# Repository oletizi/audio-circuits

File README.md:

# Audio Circuits

A collection of audio circuits under development. Some are core, reusable
components meant to appear in future designs; some are designs in their own
right. Nothing here is finished software — it is hardware in progress.

## What this repository is for

**It is for carrying a circuit from a model to something buildable, with agents
doing that work end to end:**

- **A circuit is held as data** — built with `lib/model/`'s `circuit()` builder
  or read from a KiCad netlist — where it can be validated, simulated in SPICE,
  composed, partitioned and checked.
- **The KiCad and VeroRoute interfaces are driven by agents too**, which
  arrange schematics and place and route layouts for stripboard, perfboard and
  manufactured PCBs. Until 2026-10-10 this file said the opposite — that those
  were a person's work because agents are bad at hardware design. That is no
  longer the project's position; see
  `docs/superpowers/specs/2026-10-08-agent-authored-boards-design.md`.
- **What an agent never does is set the bar its own artifact is measured
  against.** Acceptance criteria come from a rule file, a spec, or a reviewing
  agent that did not produce the artifact. That constraint is the one thing kept
  from the older arrangement, because the failure it prevents is real: an agent
  that writes its own criteria from the layout it already produced will pass
  every check it set itself.

Authority runs in both directions depending on where a circuit came from. For a
circuit an agent designs, the model is authoritative and the drawing is derived
from it. The Pultec runs the other way: an existing design imported
schematic-first, with the model derived from a netlist export.

**A `.kicad_sch` is not written by code in this repository.** It is drawn by
`TOOLING.md`'s loop — copperhead drafts, akcli-kicad repairs, `kicad-cli`
renders and exports, the reviewer gives a verdict on the rendered page, and the
page is committed under `drafted/<circuit>/<board>/` beside a `RECORD.md`
carrying the sha256 the verdict is bound to.

> **This paragraph described a model-to-schematic generator at `lib/schgen/`
> with `bun run schgen` as its front door, and a superseded stub writer at
> `lib/kicad/schematic.ts` kept alive for the `transistor-preamp` round trips.
> All of it is deleted** — `lib/schgen/`, `tools/schgen/`, `tests/schgen/`,
> `lib/kicad/schematic.ts` and the three `schgen` CLI verbs — in the plan at
> `docs/superpowers/plans/2026-10-30-remove-schgen.md`, with the findings in
> `docs/research/2026-10-30-schgen-removed.md`. **The `kicad-cli` proof the stub
> was being kept for did not have to die with it — but it did change subject.**
> The old tests wrote a fresh throwaway stub from the live model and exported
> that, so they could not survive the writer; what survived is the comparison,
> and `tests/circuits/transistor-preamp-kicad-round-trip.test.ts` now runs the
> same three assertion shapes against each board's **committed** `.kicad_sch`
> under `circuits/transistor-preamp/`. **No test will again export a freshly
> written stub**; all five boards keep a live-`kicad-cli` model-against-schematic
> proof, pointed at the sheet they actually ship. **G247**, **G248** and **G81**
> measured a generator that no longer exists.

**KiCad is a primary tool here, not an optional extra.** `make check` runs
`kicad-cli` on every board on every run. Treat it the way you would a compiler.

## The documents that govern the work

Read them in this order. Each outranks the ones below it.

| | |
| --- | --- |
| [`CONSTITUTION.md`](CONSTITUTION.md) | the few principles this project does not revisit |
| [`EVALUATING-DRAWINGS.md`](EVALUATING-DRAWINGS.md) | **canonical on drawings** - who may judge one, what counts as a valid evaluation, what an agent may say about one. An agent is not a qualified reviewer, and *better*, *good*, *clean*, *readable* and *legible* are forbidden words about any drawing produced here |
| [`CLAUDE.md`](CLAUDE.md) | the conventions every circuit follows |
| [`AGENTS.md`](AGENTS.md) | the shared working rules |
| [`TOOLING.md`](TOOLING.md) | **how a schematic actually gets drawn** - the toolchain with exact versions, the copperhead-then-akcli loop, the known repair classes (it says how many, and the set is not closed), the checks that must be able to fail, and what the procedure does not yet cover |
| [`.claude/skills/drawing-a-schematic/SKILL.md`](.claude/skills/drawing-a-schematic/SKILL.md) | **the invocation of `TOOLING.md`'s procedure** - `make draught-doctor` then `make draw` for the mechanics, the measured traps and false greens in that loop, and the ordering rule for sending a render to the reviewer. It is not the criteria and does not restate `EVALUATING-DRAWINGS.md` |
| [`docs/schematic/verdicts.md`](docs/schematic/verdicts.md) | the owner's verdicts on the pages he has seen, verbatim, each bound to the sha256 of the sheet. The defects he named are the only statements of what he wants that carry authority |
| [`DEVELOPMENT-LOG.md`](DEVELOPMENT-LOG.md) | newest session first - what was done, and what went wrong doing it |

`TOOLING.md` is the procedure and **not** the criteria; `EVALUATING-DRAWINGS.md`
is the criteria, because an agent may never author the bar its own artifact is
measured against.

This repository was previously a tscircuit component package. tscircuit has
been removed entirely — see `docs/decisions/2026-09-21-why-not-tscircuit.md`
for why.

The largest single body of content is the passive Pultec EQ in
`circuits/pultec/`: Ian Thompson-Bell's "Pultec 3 Band EQ", which combines an
EQP-1 and an MEQ-5. Its model is assembled directly from a `kicad-cli` netlist
export of the schematic in that directory, independently of the `circuit()`
builder `circuits/pt2399-core/pt2399-core.ts` uses. It is **unvalidated** — no
unit has been built from it, and the model is known to be incomplete — see
`docs/pultec/provenance.md` and `docs/pultec/unresolved.md` before treating
anything computed from it as more than a model prediction.

## Project Structure

```
audio-circuits/
├── lib/
│   ├── model/            # Canonical circuit model: types, per-kind pin
│   │                     # vocabularies, validation, the circuit() builder,
│   │                     # include() composition
│   ├── kicad/            # Readers for two KiCad netlist export formats, and
│   │   │                 # the superseded stub writer (schematic.ts) - see
│   │   │                 # "Authority runs in both directions" above and
│   │   │                 # docs/known-gaps.md G248 for why it is still here
│   │   └── symbols/      # Vendored KiCad symbol definitions the stub writer
│   │                     # embeds, so its output never depends on an installed
│   │                     # KiCad - see symbols/PROVENANCE.md
│   └── sim/              # SPICE netlist generation, AC and operating-point
│       └── models/       # Device models, each with its own provenance
│
├── circuits/             # One directory per circuit, holding its authored
│   │                     # sources together - the KiCad schematic and project
│   │                     # files alongside the .ts that models them. No KiCad
│   │                     # file sits at this level; see CLAUDE.md.
│   ├── pt2399-core/      # Transcribed from the netlist of a board that was
│   │                     # physically built and works
│   ├── pultec/           # The Pultec 3-band EQ schematic, and the five
│   │                     # physicalized stripboard modules derived from it
│   ├── transistor-preamp/ # A common-emitter lab board reconfigured by
│   │                     # jumpers and trim-pots
│   ├── optical-compressor/ # An LA-2A-inspired optical compressor: three
│   │                     # blocks joined by include(), transcribed from the
│   │                     # design spec in docs/superpowers/specs/
│   └── opamp-buffer.ts   # A unity-gain TL072 buffer
│
│                         # Within a circuit: model/ for a mechanically derived
│                         # electrical model, boards/ for physicalized board
│                         # modules, generated/ for artifacts a tool rebuilds
│
├── boards/               # Perfboard directories the perfboard CLI drives,
│                         # each checking a circuit against a physical
│                         # stripboard layout in VeroRoute, e.g.
│                         # transistor-preamp-lab/
│
├── tests/                # Model, kicad, sim, circuit and reference tests
│
└── docs/                 # Design notes, specs and plans
```

## Prerequisites

- **[KiCad](https://www.kicad.org/)**, for `kicad-cli`. Required: the perfboard
  workflow re-exports each board's netlist from its KiCad schematic on every
  run (see `make/board.mk`'s `netlist-agrees`), not just once, so `kicad-cli`
  has to be present to run `make check` against a declared board. **It is
  required for `bun test` far more widely than this paragraph used to claim.**
  It said *"exactly one test"* - "KiCad reads the generated stub as the same
  circuit" in `tests/circuits/transistor-preamp-lab.test.ts` - *"and every
  other test injects `kicad-cli` out."* **Both halves are false, measured:**
  with `KICAD_CLI` pointed at a path that does not exist, **208 testcases fail
  across 55 files, 294 further tests never register at all** (144 of them in
  twelve files that leave no trace whatever), and **50 more skip**. That test
  is also **one of five bearing the same name**, one per transistor-preamp
  board. `docs/known-gaps.md` **G250** carries the six-arm measurement. What is
  true of the original sentence is its *point*: those tests invoke `kicad-cli`
  and **fail rather than skip**, because they are the only proof that KiCad
  reads this repository's committed sheets the way the circuits mean them.
  **The five per-board tests that carried that claim were named "KiCad reads
  the generated stub as the same circuit" and are deleted with the stub
  writer**; the claim moved whole to
  `tests/circuits/transistor-preamp-kicad-round-trip.test.ts` and
  `tests/circuits/drafted-kicad-round-trip.test.ts`, which run `kicad-cli` on
  the committed `.kicad_sch` instead of on a freshly written stub. The default
  assumes a standard macOS install
  (`/Applications/KiCad/KiCad.app/Contents/MacOS/kicad-cli`); override
  `KICAD_CLI` if yours lives elsewhere.
- **[Google Chrome](https://www.google.com/chrome/)** (or another
  Chromium-family browser), for printing a build guide. Required by `make
  guide`, which renders `guide.html` to the guide's own pages with it -
  printing is part of this build system rather than a manual step afterwards,
  so a missing converter **refuses by name** instead of writing a packet with
  no PDF. It is
  also required for `bun test`: exactly one test, "the real converter prints a
  multi-page PDF from a page with the guide's print CSS" in
  `tests/guide/print-pdf.test.ts`, invokes it and **fails** (never skips) when
  it cannot find it, because Chrome's headless flags have changed across
  versions and it is the only proof that the flags this repository passes
  still produce a PDF. **That "exactly one" is measured and exact**: masking
  `HTML_TO_PDF` gives **one** failing testcase, that one, and nothing
  unregistered (**G250**'s `nochrome` arm). The default assumes a standard macOS install
  (`/Applications/Google Chrome.app/Contents/MacOS/Google Chrome`); override
  `HTML_TO_PDF` if yours lives elsewhere.
- **[qpdf](https://qpdf.sourceforge.io/)** (`brew install qpdf`), for merging
  the schematic page into a build guide so a board's packet is one printable
  document. Required by `make guide`, and by `bun test`:
  `tests/guide/merge-pdf.test.ts` and `tests/guide/single-document.test.ts`
  invoke it and **fail rather than skip**, because they are the only proof that
  the arguments this repository passes still merge, and that the inserted page
  is neither dropped nor resized. qpdf rather than `pdfunite` or `gs` for two
  stated reasons: `gs` re-distills the content streams, which is a re-render of
  an approved drawing, and qpdf is the one that will also report the page count
  and every page's size, which is what the merge is verified with. The default
  assumes Homebrew (`/opt/homebrew/bin/qpdf`, then `/usr/local/bin/qpdf`);
  override `PDF_MERGE` if yours lives elsewhere.
- **Homebrew's `qt@5`** (`brew install qt@5`), needed to build the VeroRoute
  fork the perfboard tooling drives. It is keg-only, which is why the tooling
  locates it via `brew --prefix qt@5` rather than expecting `qmake` on `PATH` -
  there is nothing to configure once it's installed.
- **Node and npm** (`npm`, and `npx` for anything that still reaches for it),
  which `draughting/install.sh` needs for `npm ci` in the copperhead checkout
  and which copperhead's own CLI runs under - the `tsx` that runs it is a
  devDependency of that checkout, installed by that `npm ci`. Measured here on
  node `v22.19.0`. Listed because the final review's M-8 found the install and
  draw paths both depend on it while this list named neither; `TOOLING.md`'s
  toolchain table already carried it.
- **copperhead, akcli-kicad, numpy and Pillow**, the schematic-drawing
  toolchain `TOOLING.md`'s loop runs. `draughting/install.sh` installs the
  pinned versions `draughting/tools.lock.json` names into
  `draughting/copperhead` and `draughting/venv-akcli` - fixed locations, not an
  override - and `make draught-doctor` reports any disagreement between that
  lock and what is actually installed.

  **THIS SAID "NEITHER IS REQUIRED FOR `bun test`" AND THAT WAS FALSE - the
  final review's I-4.** `tools/cli/draw.ts` checks the whole lock before it
  does anything else and refuses on any disagreement, and
  `tests/draught/draw.test.ts` drives two real draws expecting exit 0. The
  right statement is the one this list already makes for `kicad-cli`, Chrome
  and qpdf: **the drawing toolchain is required for `bun test`, and the tests
  that need it fail rather than skip.** It is required for drawing a schematic
  too, which is what the old sentence was reaching for.

  **Each piece was measured separately, because "the toolchain" is four things
  and a prerequisite claim about a set is not a measurement of its members.**
  Running `tests/draught/` with one piece removed and the rest present:

  | removed | what `bun test` does |
  | --- | --- |
  | `numpy` from the venv | **7 fail by name.** Nothing erased |
  | the `akcli` console script | **5 fail by name.** Nothing erased |

  In both arms four of the failures are `make draw` tests whose own subject is
  a refusal message or an intent mismatch: `runDraw` checks the whole lock
  before it does anything else, so a missing tool fails them for a reason that
  has nothing to do with what they test. That is the gate's granularity, not a
  defect in those tests, and `tools/cli/draw.ts` records the question it
  raises.
- **[Bun](https://bun.sh/)**, for the runtime and the test suite.
- **One npm RUNTIME dependency you need, installed by `bun install` rather than
  by you**: `eecircuit-engine`, the vendored SPICE engine. It pulls in nothing
  transitively and ships its own types, so there is nothing to configure.

  **`elkjs` 0.9.3 is still declared in `package.json` and NOTHING IMPORTS IT.**
  It was the deleted generator's layout backend; the only remaining mentions of
  it in the tree are that declaration, `bun.lock` and the research documents.
  Recorded rather than quietly dropped, because removing a declared dependency
  is a `package.json` change and this was a prose pass: **the dependency is
  dead weight, not a prerequisite**, and `docs/known-gaps.md` G183's note on
  constructing it under Bun no longer applies to anything here.
- **No `SCHGEN_SOURCE`, and there is nothing to set.** This list carried that
  environment variable as a prerequisite for eight tests in
  `tests/schgen/port-fidelity.test.ts`, which proved every file under
  `lib/schgen/` was still a mechanical port of its `digital-pedal-platform`
  source. **That file and the tree it guarded are deleted**, nothing in the
  repository reads the variable, and a `bun test` on a fresh machine no longer
  has those eight failures in its baseline. `docs/known-gaps.md` G110 and
  G250's `noschgen` arm measured a prerequisite that no longer exists.

Nothing else needs setting up: the perfboard tooling builds and locates the
VeroRoute fork itself, and none of the rest of this requires an environment
variable. If you want to point at your own builds instead, `VEROROUTE`,
`QMAKE`, `KICAD_CLI` and `HTML_TO_PDF` are overrides, not required setup.

### Which of these a green `bun test` is NOT evidence about

**A missing prerequisite does not always produce a failure. Two of the five
make tests DISAPPEAR, and the suite's printed file count does not move when
they do** - so `3672 pass / 0 fail` in a tree missing one of them is a true
statement about a smaller suite than the number suggests. Measured over six
full-suite arms; `docs/known-gaps.md` **G250** carries the table, the method and
the per-file losses.

| prerequisite | what its absence does to `bun test` |
| --- | --- |
| **`kicad-cli`** | **ERASES 294 tests**, 144 of them in twelve files that leave no `testsuite` element, no name and no failure; 208 further testcases fail by name; 50 skip |
| **the VeroRoute binary** | **ERASES 48 tests**, 6 of them with no trace at all; 77 testcases fail by name |
| Google Chrome | fails **1** test, by name. Nothing erased |
| Homebrew `qt@5` | **nothing at all** - the suite exits 0. It is needed to BUILD the VeroRoute binary, not to use one that exists |

**This table had a fifth row, `SCHGEN_SOURCE`**, measured as eight named
failures in one file with nothing erased. Both the file and the variable are
deleted; the row is removed rather than kept as a prerequisite nobody can
satisfy. The other four rows are unchanged and were not re-measured in that
change, so they remain G250's figures with G250's date on them.

**The rule behind the table is where the prerequisite is resolved, not which
prerequisite it is**: resolved inside a test it fails loudly, resolved at a test
file's module scope it takes the rest of the file with it. If you are comparing
two suite runs, compare the junit reports' per-file testcase counts; `Ran N
tests` under-reports the gap by the number of unhandled errors, and `across N
files` does not move at all.

## Setting up a checkout

Three of the prerequisites above are built or installed into the checkout
itself, under gitignored directories, so **every clone and every git worktree
needs them once**, after the system tools are in place:

```bash
bun install            # node_modules, including the vendored SPICE engine
make veroroute         # clone and build the VeroRoute fork veroroute.pin names,
                       # into .tools/ - a Qt5 C++ build, so it takes a while
draughting/install.sh  # copperhead and akcli-kicad at the versions
                       # draughting/tools.lock.json pins
make draught-doctor    # confirm the drawing toolchain agrees with that lock
bun test
```

**After a pull or merge that changes `veroroute.pin`, run `make veroroute`
again before `bun test`.** `make check` rebuilds a stale binary for you,
because it depends on the `veroroute` target, but `bun test` does not. It
runs whatever is already in `.tools/`, and a binary built at an older pin can
fail tests in confusing ways. A test that calls a flag the old binary lacks,
such as `--materialize`, shows up as `veroroute ... exited -1` or as a test
timing out at 5000 ms, not as "rebuild the fork". The same applies to
`draughting/install.sh` when `draughting/tools.lock.json` changes:
`make draught-doctor` names any disagreement.

## Usage

```bash
bun install
bun test           # the full suite, including the SPICE simulations and the
                   # tests that invoke kicad-cli directly (see Prerequisites)
bun run typecheck
```

**There is no verb that writes a schematic, and `bun run schgen` is gone.**
It had two verbs, `check` and `generate`, over a design module exporting a
`DesignSpec`; all three verbs, the generator behind them and the one fixture
design in the tree were deleted with
`docs/superpowers/plans/2026-10-30-remove-schgen.md`. **G165**'s look at what it
drew is a look at deleted output.

A schematic is drawn by hand-running [`TOOLING.md`](TOOLING.md)'s loop and is
approved by the reviewer, never by a check. What `bun test` holds is the other
direction: `tests/circuits/drafted-kicad-round-trip.test.ts` and
`tests/circuits/transistor-preamp-kicad-round-trip.test.ts` export committed
sheets with the real `kicad-cli` and compare them against the models, **by
content, never by timestamp**.

Circuits are checked against real, physically-built layouts through the
perfboard workflow. `make check`, run from a board's directory (e.g.
`boards/pt2399-core`) or from the repository root to check every declared
board, is that workflow's front door - see `make help` for the rest of it.

`make guide`, run from a declared board's directory (e.g.
`boards/transistor-preamp-staged`), writes that board's printable build
packet into `<board>/guide/`: two component-side layout SVGs (by designator
and by value), a mirrored copper-side SVG of cuts and solder bridges, and a
`guide.html` that embeds all three images with a build checklist (in build
order: ICs and transistors, resistors and trim-pots, capacitors, wire links,
wire-to-board junctions, solder bridges, cuts) and, where the circuit module
declares them, a power-up table of expected DC voltages - **plus `guide.pdf`,
which is ONE printable document and the only file you take to the bench.** It
is that page printed, with the board's black-and-white schematic merged in as
its **page 2** on every board that has a schematic; the header's `Schematic`
row names that page. There is no second PDF: the packet used to be an
eleven-page `guide.pdf` and a one-page `schematic.pdf` beside it with nothing
saying the stack was two documents, and the owner asked for one
(2026-10-30: *"merge them. I want a single printable document"*).

Printing and merging are both part of this build system, not steps done by
hand afterwards: the converter is a Chromium-family browser resolved through
the `HTML_TO_PDF` make variable and the merge tool is a qpdf-compatible binary
resolved through `PDF_MERGE`, each exactly as `kicad-cli` is through
`KICAD_CLI` (see `make help`). A converter or merge tool that is missing, that
fails, or that exits 0 having produced nothing usable refuses by name rather
than leaving a packet whose document is quietly absent - and the merge is
checked against the artifact rather than the exit status, because a merge that
**drops** the schematic page still writes a valid PDF and still exits 0. The
page count and every page's size are read back from the merged file, so a
dropped page or a page the tool **resized** is a refusal. **Nothing is ever
scaled to fit**: a schematic page on paper other than US Letter goes in at its
own size and the document says so on page one. `guide/` is regenerated whole on every run, is
git-ignored, and is never hand-edited; the command refuses to write a packet
when the layout has unresolved cuts, an unplaced part, or disagrees with the
circuit it claims to be.

`make bom`, run from a declared board's directory, keeps that board's parts
list. It reads the board's circuit module (including its `bomConditions()`
export, the operating point resistor dissipation is simulated at), the
board's `bom.json` (which catalog part fills each line, the extras, and the
purchasing mode: a prototype names a `stockQuantity`, bought of every part
the catalog marks `stock`, rounded up to the next listed price break - but
only at or below `maxStockUnitPrice`, and only while each supplier's order
stays within `maxStockOverage` over the same order at covered quantities,
the costliest bulk buys set aside first) and the shared catalog in `parts/`. It derives what the
board needs from the circuit, reports the lines with nothing chosen, choices
the circuit no longer has, chosen parts that no longer meet their line
(naming the field - an active device fits by its catalog `specs.type`, never
its order code `mpn`), unknown catalog ids, and prices older than 45 days, then
rewrites the board's `BOM.md`. It exits non-zero until every line is chosen
and met. It never edits `bom.json` or the catalog: choices are made by a
person or the part-researcher agent. A board with no `bom.json` is refused,
naming the file to create; the minimal one is
`{ "purchasing": { "mode": "prototype", "shrinkage": 0.1, "stockQuantity": 100, "maxStockUnitPrice": 0.15, "maxStockOverage": 0.5 }, "lines": {}, "extras": [] }`.
`BOM.md` ends with a "Bulk buys" note: which parts are bought in bulk, and
which are not and why; the report lists the latter as information only.
For a board with a `bom.json`, `make check` also fails when the committed
`BOM.md` differs from a fresh rendering, a chosen part no longer meets its
line, or `bom.json` names a catalog part that does not exist; unchosen lines and stale prices do not fail `check`, and boards
without `bom.json` are unaffected.

`bun run parts` reads supplier data through Mouser's Search API and
Digi-Key's Product Information API (both official): `lookup <mpn>` for one
exact part's supplier part numbers, stock, price breaks and links at both
suppliers (Digi-Key: one listing per packaging); `search <keywords...>` for
candidates; `source <mpn> --supplier mouser|digikey --use <use> [--sku <part
number>]` to print a catalog source ready to paste; `refresh [<catalog
id>...]` to update the catalog's Mouser and Digi-Key prices in place (it
writes nothing unless every lookup succeeds). `--supplier` narrows any verb
to one supplier. Keys are read from `~/.config/mouser/mouser-credentials.txt`
and `~/.config/digikey/digikey-credentials.txt` and never printed; see
`docs/parts/sourcing-notes.md`.

A new board's KiCad schematic is **drawn**, not generated: [`TOOLING.md`](TOOLING.md)
is the procedure and [`EVALUATING-DRAWINGS.md`](EVALUATING-DRAWINGS.md) binds
before it. The committed schematics under `circuits/` were arranged by hand and
nothing regenerates them; the drawn pages live under `drafted/<circuit>/<board>/`
with their verdicts in [`docs/schematic/verdicts.md`](docs/schematic/verdicts.md).
**This paragraph said a new board's schematic comes from `bun run schgen`, and
cited G247 for which boards that generator would accept** - the verb and the
generator are deleted, so the question G247 answered is not one anybody can ask
of this tree.

## How the Pultec reference is validated

`circuits/pultec/electrical/three-band.ts` is not compared against any board or module —
none currently exist for it. What "validated" means here is narrower:

- **Topology** comes from an exact `kicad-cli` netlist export of a board that
  was actually manufactured. **Values** come from Thompson-Bell's documentation.
  The two agree on every capacitor position, which is what makes the reference
  evidence rather than a transcription. See `docs/pultec/provenance.md` for
  the corroboration in full.
- `tests/pultec/three-band.test.ts` checks the network is structurally
  valid and spot-checks component values against the documentation.
- `tests/pultec/partition.test.ts` checks that a hypothetical split of the
  reference into per-section modules (`circuits/pultec/partition.ts`) would
  own every element exactly once and recompose to the same network — a
  consistency check on the model, not a comparison against anything built.
- `tests/pultec/ac.test.ts` runs the network through SPICE across a matrix
  of control settings and checks the frequency response against hand-derived
  analytic values and the documented curve shapes.

None of this touches real hardware or a real PCB. See `docs/pultec/provenance.md`
("UNVALIDATED") and `docs/pultec/unresolved.md` item 1.

### Discrete inductors

The reference models the two multi-tapped coils as nine discrete inductors —
the hi boost section's four taps and the mid section's five — rather than as
tapped windings. The tap nets become internal nodes in the model. This removed
a modelling caveat about winding coupling between taps; see
`docs/pultec/unresolved.md` item 7 for what was retired and why.

The inductors are specified electrically rather than by part number — values,
±20% tolerance, DCR — in `docs/pultec/values.md`, together with the
measurements behind those limits. Nothing physical has been measured against
them; see `docs/pultec/unresolved.md`.

All eleven mid frequencies are modelled. A build that wants fewer would leave
positions unpopulated, because a position designed out of the model needs the
model changed to recover it — but no build exists yet to make that call.

## Writing a circuit

A circuit is a function that returns a `Network`:

```ts
export function myStage(): Network {
  return circuit()
    .resistor("input_bias_resistor", "10k", { a: "IN", b: "GND" })
    .port("input", "IN")
    .port("ground", "GND")
    .done()
}
```

Circuits compose with `include()`, which binds every declared port explicitly —
there are no implicit global nets, not even ground. Component ids are semantic
(`input_bias_resistor`, never `R1`); reference designators belong to KiCad.

**Give it a directory.** A circuit lives in `circuits/<circuit-name>/`, and its
authored sources sit there together — the `.ts` above alongside the
`.kicad_sch` and `.kicad_pro` if it has them. No KiCad file belongs at the top
level of `circuits/`, and an editable schematic never belongs under
`reference/`, which is for derived artifacts and analysis. The test is whether
the file will be *edited* here: if it will, it is a source.

`CLAUDE.md` has the conventions in full.

## Open questions

`docs/pultec/unresolved.md` is the list, kept deliberately rather than
tidied away. The two that matter most to anyone building this:

- **R3 is fitted at 4K7**, the value the documentation gives for the build with
  no inductors. An inductive build calls for nominally 470R, a difference of
  about 5 dB of maximum high boost and half the Q. One resistor.
- **Nothing here has been measured against hardware.** Every figure is
  model-derived.

## References

- [multi-channel-preamp](https://github.com/oletizi/multi-channel-preamp) — where the
  Pultec schematic and documentation came from originally. **This is history, not a
  dependency:** both are vendored under `circuits/pultec/` and `docs/pultec/`, nothing here reads
  anything from that repository, and it has its own purpose and lifecycle. The only
  external code this project depends on is the pinned VeroRoute fork.
- `docs/pultec/` — the modularization plan and its review. **Superseded as software
  instruction** — its `lib/passives/`, `lib/export/` and tscircuit references describe a
  layout this repository no longer has; each file carries a banner saying so. Its
  electrical content still stands.
- `docs/decisions/` — recorded architecture decisions, including why tscircuit
  was dropped
- `docs/schematic/` — the research the schematic-generation program rests on:
  what the published standards say about readable schematics, what already
  exists in agent and programmatic schematic generation, and how one working
  generator actually arrived at drawings somebody accepted.
  **`docs/schematic/README.md` is the index, and it records how far each of the
  three can be trusted** — they differ sharply, and the weakest verified nothing
  by running it.
- `docs/superpowers/specs/` — design documents for individual changes

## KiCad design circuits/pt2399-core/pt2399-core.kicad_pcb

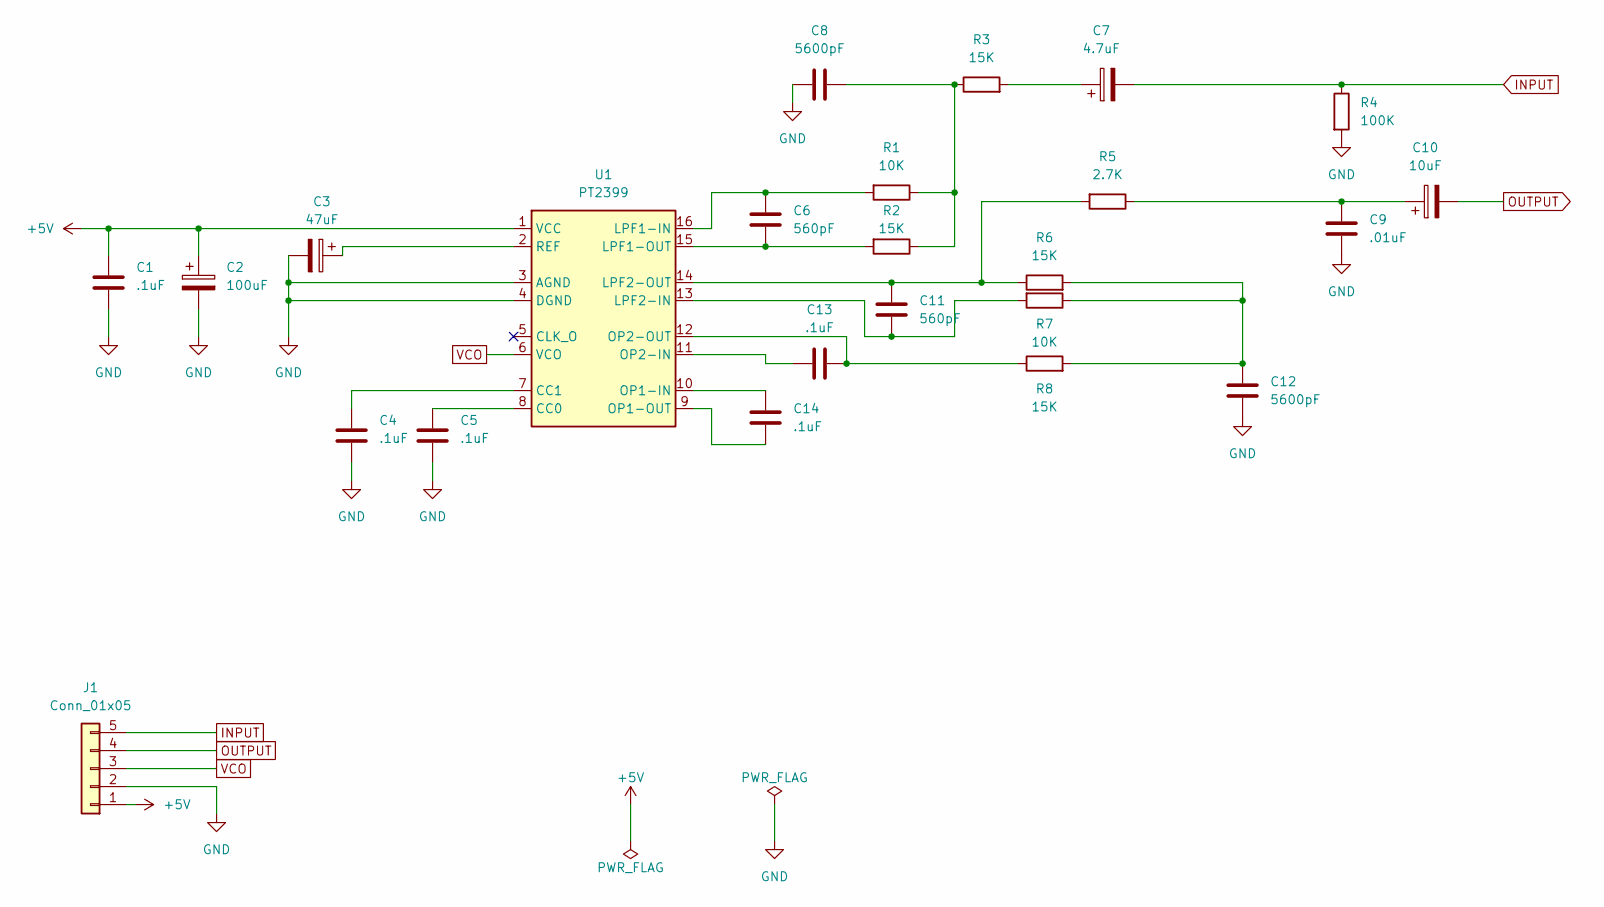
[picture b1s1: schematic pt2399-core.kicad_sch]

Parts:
C1, C4, C5, C13, C14: .1uF; C_Disc_D5.0mm_W2.5mm_P2.50mm
C2: 100uF; CP_Radial_D5.0mm_P2.00mm
C3: 47uF; CP_Radial_D6.3mm_P2.50mm
C6, C11: 560pF; C_Disc_D5.0mm_W2.5mm_P2.50mm
C7: 4.7uF; CP_Radial_D5.0mm_P2.50mm
C8, C12: 5600pF; C_Disc_D5.0mm_W2.5mm_P2.50mm
C9: .01uF; C_Disc_D5.0mm_W2.5mm_P2.50mm
C10: 10uF; CP_Radial_D5.0mm_P2.50mm
J1: Conn_01x05; PinHeader_1x05_P2.54mm_Vertical
R1, R7: 10K; R_Axial_DIN0207_L6.3mm_D2.5mm_P10.16mm_Horizontal
R2, R3, R6, R8: 15K; R_Axial_DIN0207_L6.3mm_D2.5mm_P10.16mm_Horizontal
R4: 100K; R_Axial_DIN0207_L6.3mm_D2.5mm_P10.16mm_Horizontal
R5: 2.7K; R_Axial_DIN0207_L6.3mm_D2.5mm_P10.16mm_Horizontal
U1: PT2399; DIP-16_W7.62mm

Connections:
+5V: C1.1, C2.1, J1.1, U1.1 (VCC)
GND: C1.2, C2.2, C3.2, C4.2, C5.2, C8.1, C9.2, C12.2, J1.2, R4.2, U1.3 (AGND), U1.4 (DGND)
INPUT: C7.2, J1.5, R4.1
unnamed: C7.1, R3.2
unnamed: C8.2, R1.1, R2.1, R3.1
unnamed: C9.1, C10.1, R5.1
unnamed: C12.1, R6.2, R7.1, R8.2
unnamed: C5.1, U1.8 (CC0)
unnamed: C4.1, U1.7 (CC1)
unnamed: C6.1, R1.2, U1.16 (LPF1-IN)
unnamed: C6.2, R2.2, U1.15 (LPF1-OUT)
unnamed: C11.1, R7.2, U1.13 (LPF2-IN)
unnamed: C11.2, R5.2, R6.1, U1.14 (LPF2-OUT)
unnamed: C14.2, U1.10 (OP1-IN)
unnamed: C14.1, U1.9 (OP1-OUT)
unnamed: C13.1, U1.11 (OP2-IN)
unnamed: C13.2, R8.1, U1.12 (OP2-OUT)
unnamed: C3.1, U1.2 (REF)
OUTPUT: C10.2, J1.4
VCO: J1.3, U1.6 (VCO)

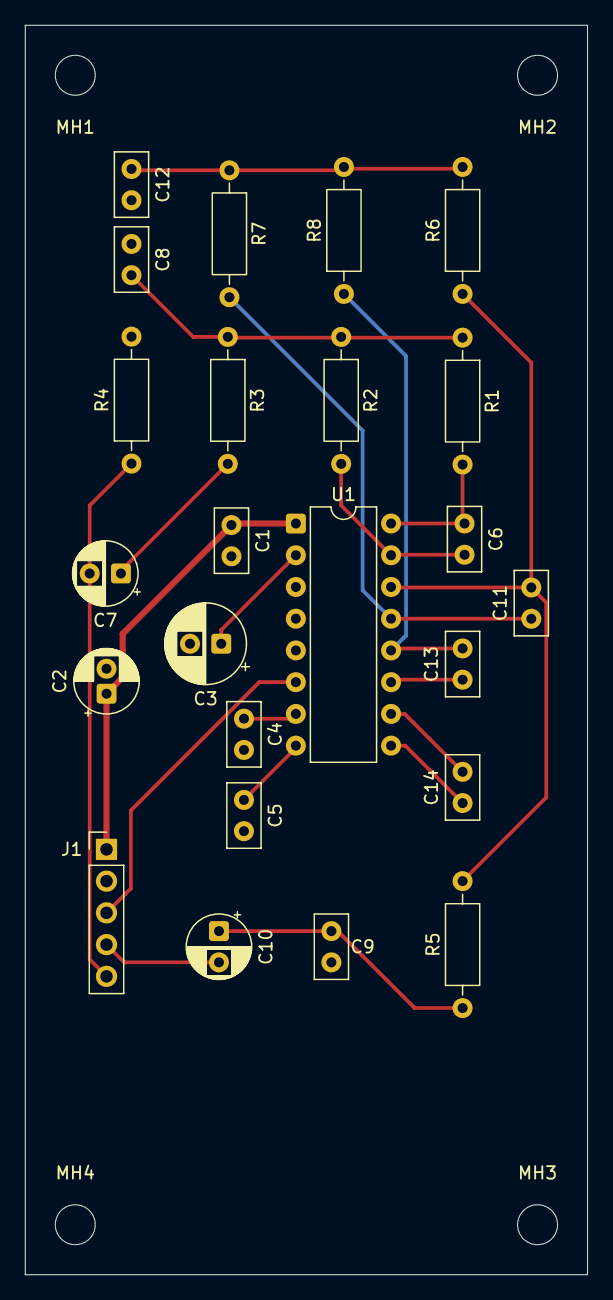
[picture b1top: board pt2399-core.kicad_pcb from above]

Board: 2 copper layers, 45.0 x 100.0 mm, 28 parts (0 on the bottom side), 20 nets.

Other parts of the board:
MH1, MH2, MH3, MH4: MountingHole_3.2mm_M3_Washer7.0mm
